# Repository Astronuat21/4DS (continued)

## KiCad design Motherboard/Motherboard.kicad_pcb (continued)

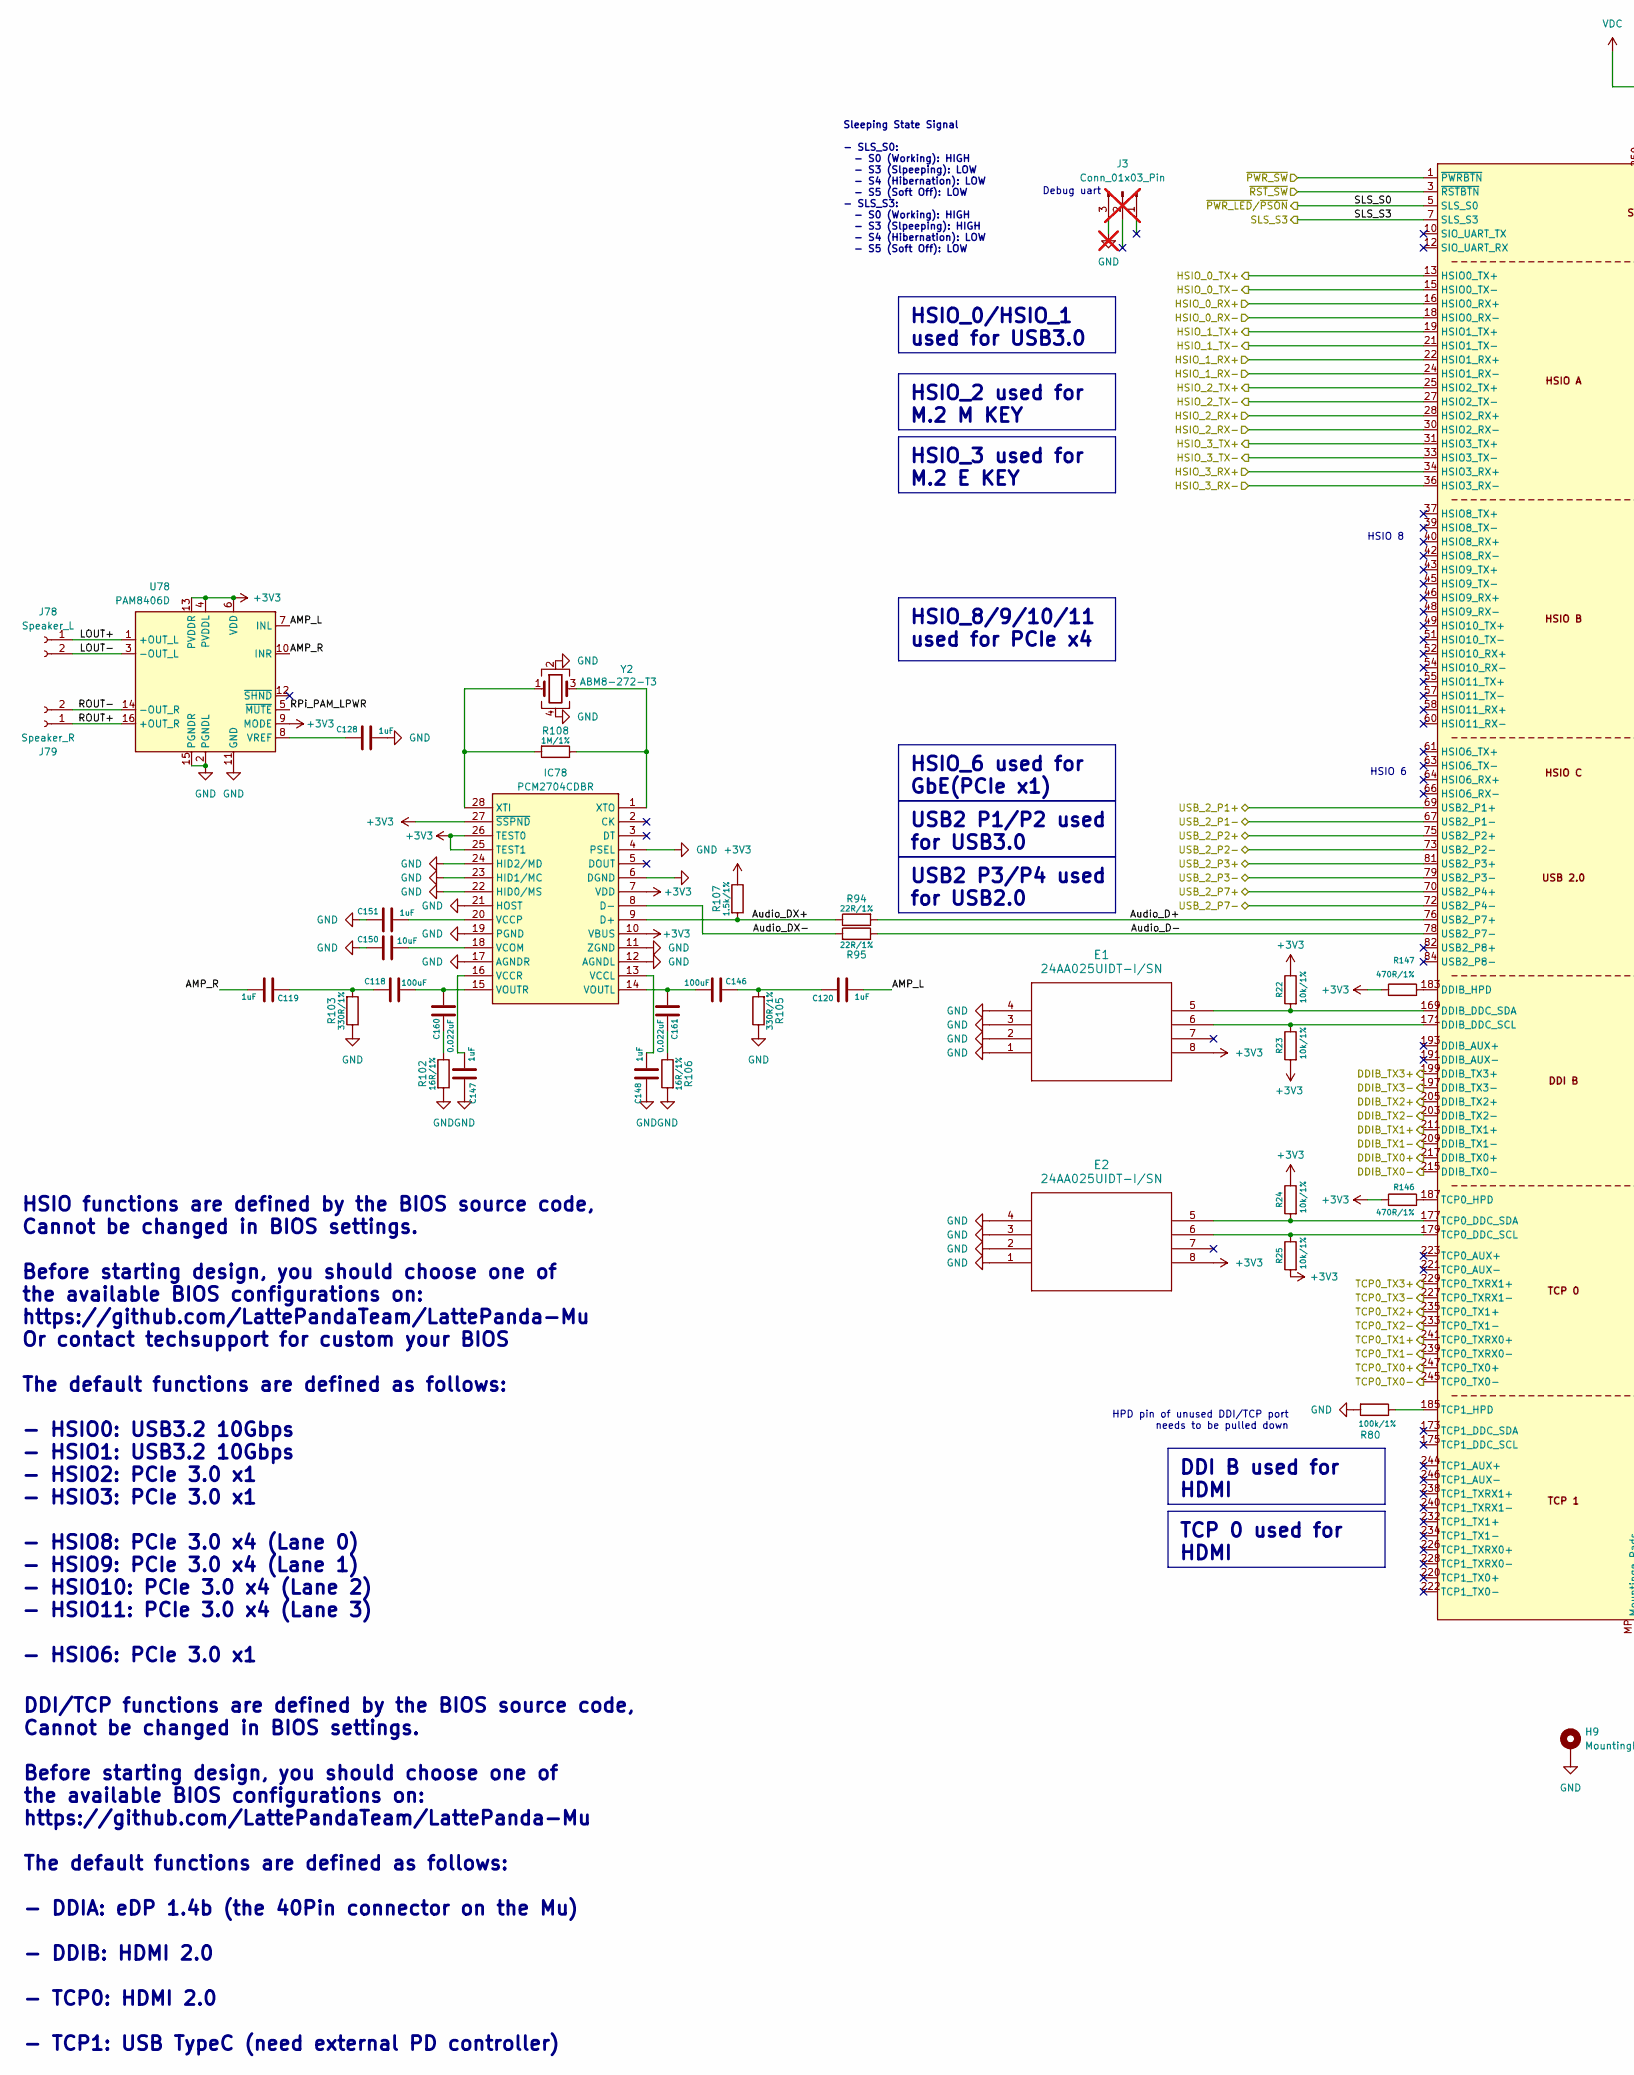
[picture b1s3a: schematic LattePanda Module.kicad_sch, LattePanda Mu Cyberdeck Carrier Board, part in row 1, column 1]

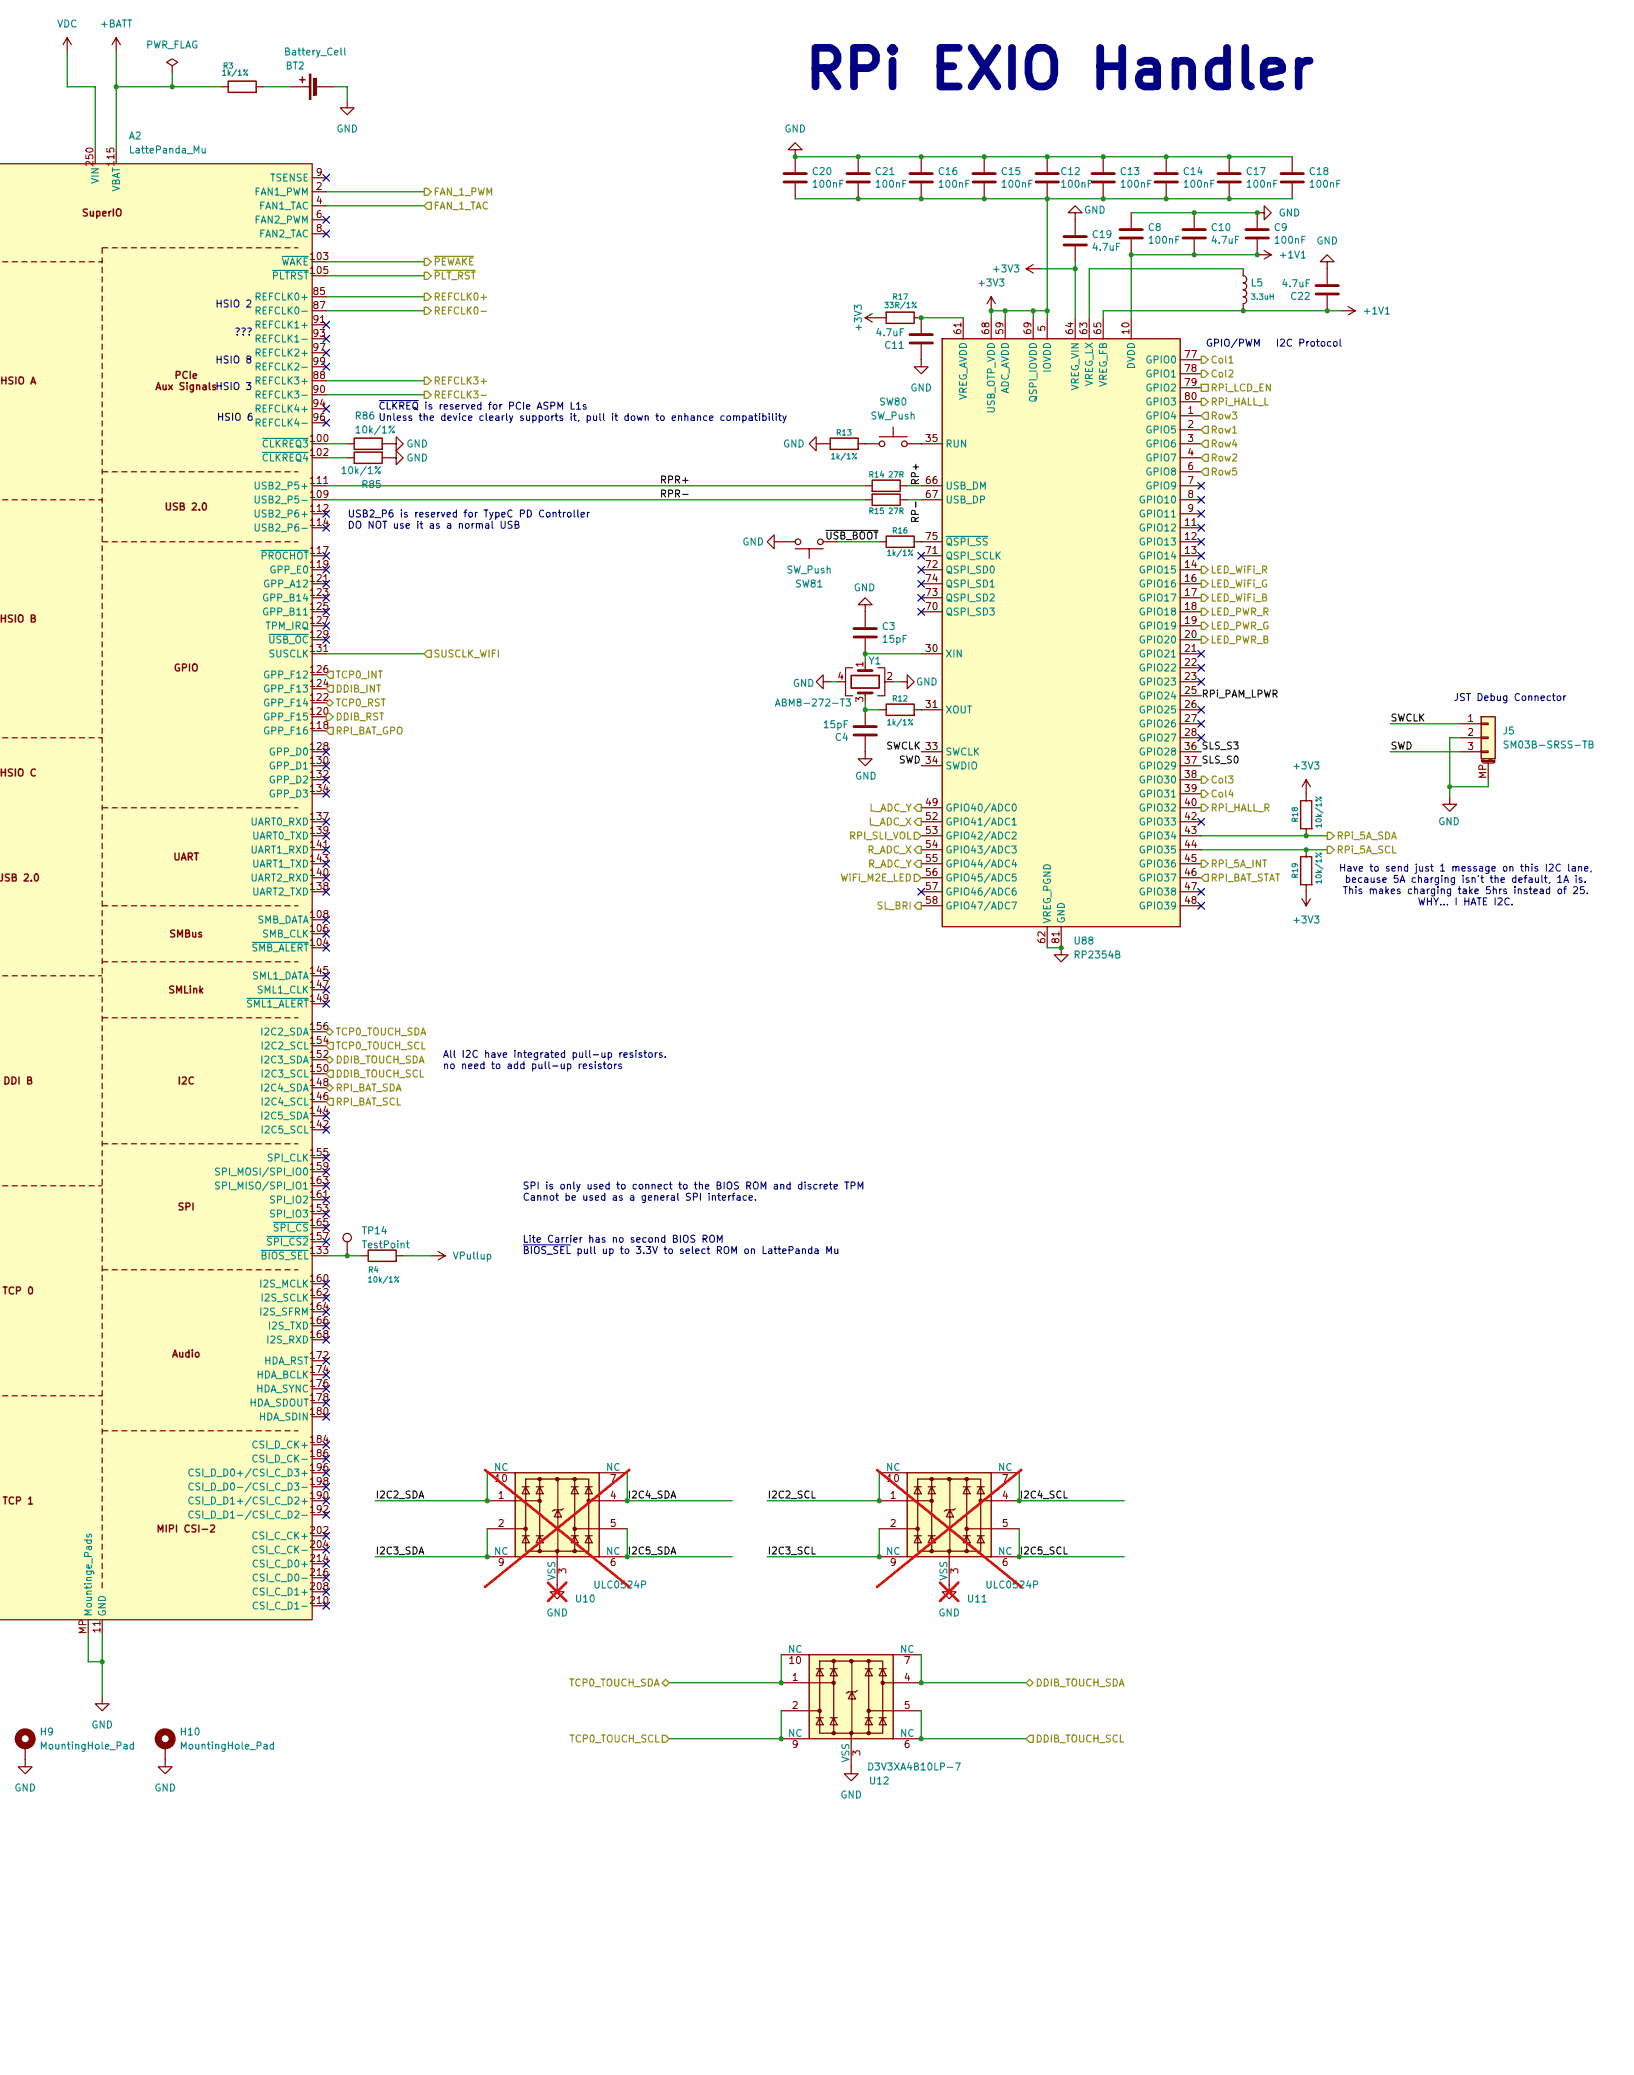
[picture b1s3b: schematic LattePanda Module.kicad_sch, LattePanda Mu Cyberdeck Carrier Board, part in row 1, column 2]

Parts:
A2: LattePanda_Mu; LattePanda_Module_H8.0mm_Horizontal; MPN ADDR0207-P001A
BT2: Battery_Cell; Battery_Holder_CR1220_S8411-45R; MPN BS-12-B3AA003
C3, C4: 15pF; C_0603_1608Metric; MPN C0603C150K4RACTU
C8, C9, C12, C13, C14, C15, C16, C17, C18, C20, C21: 100nF; C_0402_1005Metric; MPN CC0402MRX5R6BB104
C10, C11, C19, C22: 4.7uF; C_0402_1005Metric; MPN 0402X475M100NT
C118, C146: 100uF; C_1210_3225Metric; MPN GRM32ER61A107ME20L
C119, C120, C128, C147, C148, C151: 1uF; C_0402_1005Metric; MPN TCC0402X5R105M100AT
C150: 10uF; C_0402_1005Metric; MPN GMC04X5R106M10NT
C160, C161: 0.022uF; C_0603_1608Metric; MPN C0603X5R100-223KNP
E1, E2: 24AA025UIDT-I/SN; SOIC8-N_MC_MCH; MPN 24AA025UIDT-I/SN
H9, H10: MountingHole_Pad; MountingHole_3mm_M2_Pad_TopOnly; MPN SMTWEM225STR
IC78: PCM2704CDBR; SOP65P780X200-28N; MPN PCM2704CDBR
J3: Conn_01x03_Pin; PinHeader_1x03_P2.54mm_Vertical; not fitted
J5: SM03B-SRSS-TB; JST_SH_SM03B-SRSS-TB_1x03-1MP_P1.00mm_Horizontal; MPN SM03B-SRSS-TB
J78: Speaker_L; Molex_PicoBlade_53047-0210_1x02_P1.25mm_Vertical; MPN 0530470210
J79: Speaker_R; Molex_PicoBlade_53047-0210_1x02_P1.25mm_Vertical; MPN 0530470210
L5: 3.3uH; L_pol_2016; MPN AOTA-B201610S3R3-101-T
R3, R12, R13, R16: 1k/1%; R_0402_1005Metric; MPN CQ02WGF1001TCE
R4, R18, R19, R22, R23, R24, R25, R85, R86: 10k/1%; R_0402_1005Metric; MPN MCR01MZPF1002
R14, R15: 27R; R_0402_1005Metric; MPN AC0402FR-0727RL
R17: 33R/1%; R_0402_1005Metric; MPN AF0402FR-0733RL
R80: 100k/1%; R_0402_1005Metric; MPN SFR01MZPF1003
R94, R95: 22R/1%; R_0603_1608Metric; MPN 0603WAF220JT5E
R102, R106: 16R/1%; R_0805_2012Metric; MPN 0805W8F160JT5E
R103, R105: 330R/1%; R_0805_2012Metric; MPN TC0525F3300T5G
R107: 1.5k/1%; R_0805_2012Metric; MPN 0805W8F1501T5E
R108: 1M/1%; R_0603_1608Metric; MPN KTR03EZPF1004
R146, R147: 470R/1%; R_0402_1005Metric; MPN SFR01MZPF4700
SW80, SW81: SW_Push; SW_SPST_B3U-1000P; MPN B3U-1000P
TP14: TestPoint; TestPoint_Pad_D1.5mm
U10, U11: ULC0524P; Diodes_UDFN-10_1.0x2.5mm_P0.5mm; not fitted
U12: D3V3XA4B10LP-7; Diodes_UDFN-10_1x2.5mm_P0.5mm; MPN D3V3XA4B10LP-7
U78: PAM8406D; SOIC-16_3.9x9.9mm_P1.27mm
U88: RP2354B; QFN-80-1EP_10x10mm_P0.4mm_EP3.4x3.4mm; MPN SC1512-A4
Y1, Y2: ABM8-272-T3; Crystal_SMD_3225-4Pin_3.2x2.5mm; MPN ABM8-272-T3

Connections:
+1V1: C8.2, C9.2, C10.2, C22.1, L5.2, U88.10 (DVDD), U88.32 (DVDD), U88.51 (DVDD), U88.65 (VREG_FB)
+3V3: C12.2, C13.2, C14.2, C15.2, C16.2, C17.2, C18.2, C19.2, C20.2, C21.2, E1.8, E2.8, IC78.7 (VDD), IC78.10 (VBUS), IC78.25 (TEST1), IC78.26 (TEST0), IC78.27 (~SSPND), R17.2, R18.1, R19.2, R22.1, R23.2, R24.1, R25.2, R107.1, R146.1, R147.1, U78.4 (PVDDL), U78.6 (VDD), U78.9 (MODE), U78.13 (PVDDR), U88.5 (IOVDD), U88.15 (IOVDD), U88.24 (IOVDD), U88.29 (IOVDD), U88.41 (IOVDD), U88.50 (IOVDD), U88.59 (ADC_AVDD), U88.60 (IOVDD), U88.64 (VREG_VIN), U88.68 (USB_OTP_VDD), U88.69 (QSPI_IOVDD), U88.76 (IOVDD); also elsewhere on the board
+BATT: A2.115 (VBAT), R3.1
/EXIO/Col1: U88.77 (GPIO0); also elsewhere on the board
/EXIO/Col2: U88.78 (GPIO1); also elsewhere on the board
/EXIO/Col3: U88.38 (GPIO30); also elsewhere on the board
/EXIO/Col4: U88.39 (GPIO31); also elsewhere on the board
/EXIO/LED_PWR_B: U88.20 (GPIO20); also elsewhere on the board
/EXIO/LED_PWR_G: U88.19 (GPIO19); also elsewhere on the board
/EXIO/LED_PWR_R: U88.18 (GPIO18); also elsewhere on the board
/EXIO/LED_WiFi_B: U88.17 (GPIO17); also elsewhere on the board
/EXIO/LED_WiFi_G: U88.16 (GPIO16); also elsewhere on the board
/EXIO/LED_WiFi_R: U88.14 (GPIO15); also elsewhere on the board
/EXIO/L_ADC_X: U88.52 (GPIO41/ADC1); also elsewhere on the board
/EXIO/L_ADC_Y: U88.49 (GPIO40/ADC0); also elsewhere on the board
/EXIO/RPi_HALL_L: U88.80 (GPIO3); also elsewhere on the board
/EXIO/RPi_HALL_R: U88.40 (GPIO32); also elsewhere on the board
/EXIO/R_ADC_X: U88.54 (GPIO43/ADC3); also elsewhere on the board
/EXIO/R_ADC_Y: U88.55 (GPIO44/ADC4); also elsewhere on the board
/EXIO/Row1: U88.2 (GPIO5); also elsewhere on the board
/EXIO/Row2: U88.4 (GPIO7); also elsewhere on the board
/EXIO/Row3: U88.1 (GPIO4); also elsewhere on the board
/EXIO/Row4: U88.3 (GPIO6); also elsewhere on the board
/EXIO/Row5: U88.6 (GPIO8); also elsewhere on the board
/EXIO/SL_BRI: U88.58 (GPIO47/ADC7); also elsewhere on the board
/EXIO/SL_VOL: U88.53 (GPIO42/ADC2); also elsewhere on the board
/Fan_Temp/FAN_1_PWM: A2.2 (FAN1_PWM); also elsewhere on the board
/Fan_Temp/FAN_1_TAC: A2.4 (FAN1_TAC); also elsewhere on the board
/LattePanda Module/AMP_L: C120.1, U78.7 (INL)
/LattePanda Module/AMP_R: C119.1, U78.10 (INR)
/LattePanda Module/Audio_D+: A2.76 (USB2_P7+), R94.2
/LattePanda Module/Audio_D-: A2.78 (USB2_P7-), R95.1
/LattePanda Module/Audio_DX+: IC78.9 (D+), R94.1, R107.2
/LattePanda Module/Audio_DX-: IC78.8 (D-), R95.2
/LattePanda Module/DDIB_INT: A2.124 (GPP_F13); also elsewhere on the board
/LattePanda Module/DDIB_RST: A2.120 (GPP_F15); also elsewhere on the board
/LattePanda Module/DDIB_TOUCH_SCL: A2.150 (I2C3_SCL), U12.5, U12.6 (NC); also elsewhere on the board
/LattePanda Module/DDIB_TOUCH_SDA: A2.152 (I2C3_SDA), U12.4, U12.7 (NC); also elsewhere on the board
/LattePanda Module/DDIB_TX0+: A2.217 (DDIB_TX0+); also elsewhere on the board
/LattePanda Module/DDIB_TX0-: A2.215 (DDIB_TX0-); also elsewhere on the board
/LattePanda Module/DDIB_TX1+: A2.211 (DDIB_TX1+); also elsewhere on the board
/LattePanda Module/DDIB_TX1-: A2.209 (DDIB_TX1-); also elsewhere on the board
/LattePanda Module/DDIB_TX2+: A2.205 (DDIB_TX2+); also elsewhere on the board
/LattePanda Module/DDIB_TX2-: A2.203 (DDIB_TX2-); also elsewhere on the board
/LattePanda Module/DDIB_TX3+: A2.199 (DDIB_TX3+); also elsewhere on the board
/LattePanda Module/DDIB_TX3-: A2.197 (DDIB_TX3-); also elsewhere on the board
/LattePanda Module/HSIO_0_TX+: A2.13 (HSIO0_TX+); also elsewhere on the board
/LattePanda Module/HSIO_0_TX-: A2.15 (HSIO0_TX-); also elsewhere on the board
/LattePanda Module/HSIO_1_TX+: A2.19 (HSIO1_TX+); also elsewhere on the board
/LattePanda Module/HSIO_1_TX-: A2.21 (HSIO1_TX-); also elsewhere on the board
/LattePanda Module/HSIO_2_RX+: A2.28 (HSIO2_RX+); also elsewhere on the board
/LattePanda Module/HSIO_2_RX-: A2.30 (HSIO2_RX-); also elsewhere on the board
/LattePanda Module/HSIO_2_TX+: A2.25 (HSIO2_TX+); also elsewhere on the board
/LattePanda Module/HSIO_2_TX-: A2.27 (HSIO2_TX-); also elsewhere on the board
/LattePanda Module/HSIO_3_RX+: A2.34 (HSIO3_RX+); also elsewhere on the board
/LattePanda Module/HSIO_3_RX-: A2.36 (HSIO3_RX-); also elsewhere on the board
/LattePanda Module/HSIO_3_TX+: A2.31 (HSIO3_TX+); also elsewhere on the board
/LattePanda Module/HSIO_3_TX-: A2.33 (HSIO3_TX-); also elsewhere on the board
/LattePanda Module/LOUT+: J78.1, U78.1 (+OUT_L)
/LattePanda Module/LOUT-: J78.2, U78.3 (-OUT_L)
/LattePanda Module/REFCLK0+: A2.85 (REFCLK0+); also elsewhere on the board
/LattePanda Module/REFCLK0-: A2.87 (REFCLK0-); also elsewhere on the board
/LattePanda Module/REFCLK3+: A2.88 (REFCLK3+); also elsewhere on the board
/LattePanda Module/REFCLK3-: A2.90 (REFCLK3-); also elsewhere on the board
/LattePanda Module/ROUT+: J79.1, U78.16 (+OUT_R)
/LattePanda Module/ROUT-: J79.2, U78.14 (-OUT_R)
/LattePanda Module/RP+: R14.1, U88.66 (USB_DM)
/LattePanda Module/RP-: R15.1, U88.67 (USB_DP)
/LattePanda Module/RPI_BAT_GPO: A2.118 (GPP_F16); also elsewhere on the board
/LattePanda Module/RPI_BAT_SCL: A2.146 (I2C4_SCL); also elsewhere on the board
/LattePanda Module/RPI_BAT_SDA: A2.148 (I2C4_SDA); also elsewhere on the board
/LattePanda Module/RPI_BAT_STAT: U88.46 (GPIO37); also elsewhere on the board
/LattePanda Module/RPR+: A2.111 (USB2_P5+), R14.2
/LattePanda Module/RPR-: A2.109 (USB2_P5-), R15.2
/LattePanda Module/RPi_5A_INT: U88.45 (GPIO36); also elsewhere on the board
/LattePanda Module/RPi_5A_SCL: R19.1, U88.44 (GPIO35); also elsewhere on the board
/LattePanda Module/RPi_5A_SDA: R18.2, U88.43 (GPIO34); also elsewhere on the board
/LattePanda Module/RPi_LCD_EN: U88.79 (GPIO2); also elsewhere on the board
/LattePanda Module/RPi_PAM_LPWR: U78.5 (~MUTE), U88.25 (GPIO24)
/LattePanda Module/SLS_S3: A2.7 (SLS_S3), U88.36 (GPIO28); also elsewhere on the board
/LattePanda Module/SUSCLK_WIFI: A2.131 (SUSCLK); also elsewhere on the board
/LattePanda Module/SWCLK: J5.1, U88.33 (SWCLK)
/LattePanda Module/SWD: J5.3, U88.34 (SWDIO)
/LattePanda Module/TCP0_INT: A2.126 (GPP_F12); also elsewhere on the board
/LattePanda Module/TCP0_RST: A2.122 (GPP_F14); also elsewhere on the board
/LattePanda Module/TCP0_TOUCH_SCL: A2.154 (I2C2_SCL), U12.2, U12.9 (NC); also elsewhere on the board
/LattePanda Module/TCP0_TOUCH_SDA: A2.156 (I2C2_SDA), U12.1, U12.10 (NC); also elsewhere on the board
/LattePanda Module/TCP0_TX0+: A2.247 (TCP0_TX0+); also elsewhere on the board
/LattePanda Module/TCP0_TX0-: A2.245 (TCP0_TX0-); also elsewhere on the board
/LattePanda Module/TCP0_TX1+: A2.241 (TCP0_TXRX0+); also elsewhere on the board
/LattePanda Module/TCP0_TX1-: A2.239 (TCP0_TXRX0-); also elsewhere on the board
/LattePanda Module/TCP0_TX2+: A2.235 (TCP0_TX1+); also elsewhere on the board
/LattePanda Module/TCP0_TX2-: A2.233 (TCP0_TX1-); also elsewhere on the board
/LattePanda Module/TCP0_TX3+: A2.229 (TCP0_TXRX1+); also elsewhere on the board
/LattePanda Module/TCP0_TX3-: A2.227 (TCP0_TXRX1-); also elsewhere on the board
/LattePanda Module/USB_2_P7+: A2.70 (USB2_P4+); also elsewhere on the board
/LattePanda Module/USB_2_P7-: A2.72 (USB2_P4-); also elsewhere on the board
/LattePanda Module/WiFi_M2E_LED: U88.56 (GPIO45/ADC5); also elsewhere on the board
/LattePanda Module/~PWR_SW: A2.1 (~PWRBTN); also elsewhere on the board
/LattePanda Module/~RST_SW: A2.3 (~RSTBTN)
/LattePanda Module/~USB_BOOT: R16.1, SW81.1
/USB/CON_USB1_D_N: A2.79 (USB2_P3-)
/USB/CON_USB1_D_P: A2.81 (USB2_P3+)
/USB/CON_USB3_D_N: A2.73 (USB2_P2-); also elsewhere on the board
/USB/CON_USB3_D_P: A2.75 (USB2_P2+); also elsewhere on the board
/USB/CON_USB3_SSRX_N: A2.18 (HSIO0_RX-); also elsewhere on the board
/USB/CON_USB3_SSRX_P: A2.16 (HSIO0_RX+); also elsewhere on the board
/USB/CON_USB4_D_N: A2.67 (USB2_P1-); also elsewhere on the board
/USB/CON_USB4_D_P: A2.69 (USB2_P1+); also elsewhere on the board
/USB/CON_USB4_SSRX_N: A2.24 (HSIO1_RX-); also elsewhere on the board
/USB/CON_USB4_SSRX_P: A2.22 (HSIO1_RX+); also elsewhere on the board
/~PLT_RST: A2.105 (~PLTRST); also elsewhere on the board
/~PWR_LED/~PSON: A2.5 (SLS_S0), U88.37 (GPIO29); also elsewhere on the board
/~WAKE: A2.103 (~WAKE); also elsewhere on the board
GND: A2.11 (GND), A2.14 (GND), A2.17 (GND), A2.20 (GND), A2.23 (GND), A2.26 (GND), A2.29 (GND), A2.32 (GND), A2.35 (GND), A2.38 (GND), A2.41 (GND), A2.44 (GND), A2.47 (GND), A2.50 (GND), A2.53 (GND), A2.56 (GND), A2.59 (GND), A2.62 (GND), A2.65 (GND), A2.68 (GND), A2.71 (GND), A2.74 (GND), A2.77 (GND), A2.80 (GND), A2.83 (GND), A2.86 (GND), A2.89 (GND), A2.92 (GND), A2.95 (GND), A2.98 (GND), A2.101 (GND), A2.107 (GND), A2.110 (GND), A2.113 (GND), A2.116 (GND), A2.135 (GND), A2.136 (GND), A2.151 (GND), A2.158 (GND), A2.167 (GND), A2.170 (GND), A2.181 (GND), A2.182 (GND), A2.188 (GND), A2.189 (GND), A2.194 (GND), A2.195 (GND), A2.200 (GND), A2.201 (GND), A2.206 (GND), A2.207 (GND), A2.212 (GND), A2.213 (GND), A2.218 (GND), A2.219 (GND), A2.224 (GND), A2.225 (GND), A2.230 (GND), A2.231 (GND), A2.236 (GND), A2.237 (GND), A2.242 (GND), A2.243 (GND), A2.248 (GND), A2.249 (GND), A2.MP (Mountinge_Pads), BT2.2 (-), C3.1, C4.1, C8.1, C9.1, C10.1, C11.1, C12.1, C13.1, C14.1, C15.1, C16.1, C17.1, C18.1, C19.1, C20.1, C21.1, C22.2, C128.1, C147.2, C148.2, C150.2, C151.2, E1.1, E1.2, E1.3, E1.4, E2.1, E2.2, E2.3, E2.4, H9.1 (1_1), H10.1 (1_1), IC78.4 (PSEL), IC78.6 (DGND), IC78.11 (ZGND), IC78.12 (AGNDL), IC78.17 (AGNDR), IC78.19 (PGND), IC78.21 (HOST), IC78.22 (HID0/MS), IC78.23 (HID1/MC), IC78.24 (HID2/MD), J3.3, J5.2, J5.MP (MountPin), R13.1, R80.2, R85.2, R86.2, R102.2, R103.1, R105.1, R106.2, SW81.2, U10.3 (VSS), U10.8 (VSS), U11.3 (VSS), U11.8 (VSS), U12.3 (VSS), U12.8 (VSS), U78.2 (PGNDL), U78.11 (GND), U78.15 (PGNDR), U88.62 (VREG_PGND), U88.81 (GND), Y1.2, Y1.4, Y2.2, Y2.4; also elsewhere on the board
unnamed: A2.171 (DDIB_DDC_SCL), E1.6, R23.1
unnamed: A2.169 (DDIB_DDC_SDA), E1.5, R22.2
unnamed: A2.183 (DDIB_HPD), R147.2
unnamed: A2.179 (TCP0_DDC_SCL), E2.6, R25.1
unnamed: A2.177 (TCP0_DDC_SDA), E2.5, R24.2
unnamed: A2.187 (TCP0_HPD), R146.2
unnamed: A2.185 (TCP1_HPD), R80.1
unnamed: A2.133 (~BIOS_SEL), R4.1, TP14.1 (1_1)
unnamed: A2.100 (~CLKREQ3), R86.1
unnamed: A2.102 (~CLKREQ4), R85.1
unnamed: BT2.1 (+), R3.2
unnamed: C4.2, R12.1, Y1.3
unnamed: C118.2, C119.2, R103.2
unnamed: C120.2, C146.2, R105.2
unnamed: C160.2, R102.1
unnamed: C161.2, R106.1
unnamed: C148.1, IC78.13 (VCCL)
unnamed: C151.1, IC78.20 (VCCP)
unnamed: C147.1, IC78.16 (VCCR)
unnamed: C150.1, IC78.18 (VCOM)
unnamed: C146.1, C161.1, IC78.14 (VOUTL)
unnamed: C118.1, C160.1, IC78.15 (VOUTR)
unnamed: IC78.28 (XTI), R108.2, Y2.1
unnamed: IC78.1 (XTO), R108.1, Y2.3
unnamed: R13.2, SW80.1
unnamed: U10.1, U10.10 (NC)
unnamed: U10.2, U10.9 (NC)
unnamed: U10.4, U10.7 (NC)
unnamed: U10.5, U10.6 (NC)
unnamed: U11.1, U11.10 (NC)
unnamed: U11.2, U11.9 (NC)
unnamed: U11.4, U11.7 (NC)
unnamed: U11.5, U11.6 (NC)
unnamed: C128.2, U78.8 (VREF)
unnamed: SW80.2, U88.35 (RUN)
unnamed: C11.2, R17.1, U88.61 (VREG_AVDD)
unnamed: L5.1, U88.63 (VREG_LX)
unnamed: C3.2, U88.30 (XIN), Y1.1
unnamed: R12.2, U88.31 (XOUT)
unnamed: R16.2, U88.75 (~QSPI_SS)
VDC: A2.250 (VIN), A2.251 (VIN), A2.252 (VIN), A2.253 (VIN), A2.254 (VIN), A2.255 (VIN), A2.256 (VIN), A2.257 (VIN), A2.258 (VIN), A2.259 (VIN), A2.260 (VIN); also elsewhere on the board
VPullup: R4.2; also elsewhere on the board

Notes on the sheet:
HSIO functions are defined by the BIOS source code, Cannot be changed in BIOS settings. Before starting design, you should choose one of the available BIOS configurations on: https://github.com/LattePandaTeam/LattePanda-Mu Or contact techsupport for custom your BIOS The default functions are define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
HSIO 3
Lite Carrier has no second BIOS ROM ~{BIOS_SEL} pull up to 3.3V to select ROM on LattePanda Mu
DDI/TCP functions are defined by the BIOS source code, Cannot be changed in BIOS settings. Before starting design, you should choose one of the available BIOS configurations on: https://github.com/LattePandaTeam/LattePanda-Mu The default functions are defined as follows: - DDIA: eDP 1.4b (the 40Pin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
GPIO/PWM
HSIO 8
Sleeping State Signal - SLS_S0: - S0 (Working): HIGH - S3 (Slpeeping): LOW - S4 (Hibernation): LOW - S5 (Soft Off): LOW - SLS_S3: - S0 (Working): HIGH - S3 (Slpeeping): HIGH - S4 (Hibernation): LOW - S5 (Soft Off): LOW
HSIO 6
USB2_P6 is reserved for TypeC PD Controller DO NOT use it as a normal USB
SPI is only used to connect to the BIOS ROM and discrete TPM Cannot be used as a general SPI interface.
???
All I2C have integrated pull-up resistors. no need to add pull-up resistors
Debug uart
JST Debug Connector
~{CLKREQ} is reserved for PCIe ASPM L1s Unless the device clearly supports it, pull it down to enhance compatibility
RPi EXIO Handler
HSIO 8
Have to send just 1 message on this I2C lane, because 5A charging isn't the default, 1A is. This makes charging take 5hrs instead of 25. WHY... I HATE I2C.
I2C Protocol
HPD pin of unused DDI/TCP port needs to be pulled down
HSIO 2
HSIO_0/HSIO_1 used for USB3.0
HSIO_2 used for M.2 M KEY
HSIO_6 used for GbE(PCIe x1)
USB2 P3/P4 used for USB2.0
DDI B used for HDMI
TCP 0 used for HDMI
HSIO_3 used for M.2 E KEY
HSIO_8/9/10/11 used for PCIe x4
USB2 P1/P2 used for USB3.0

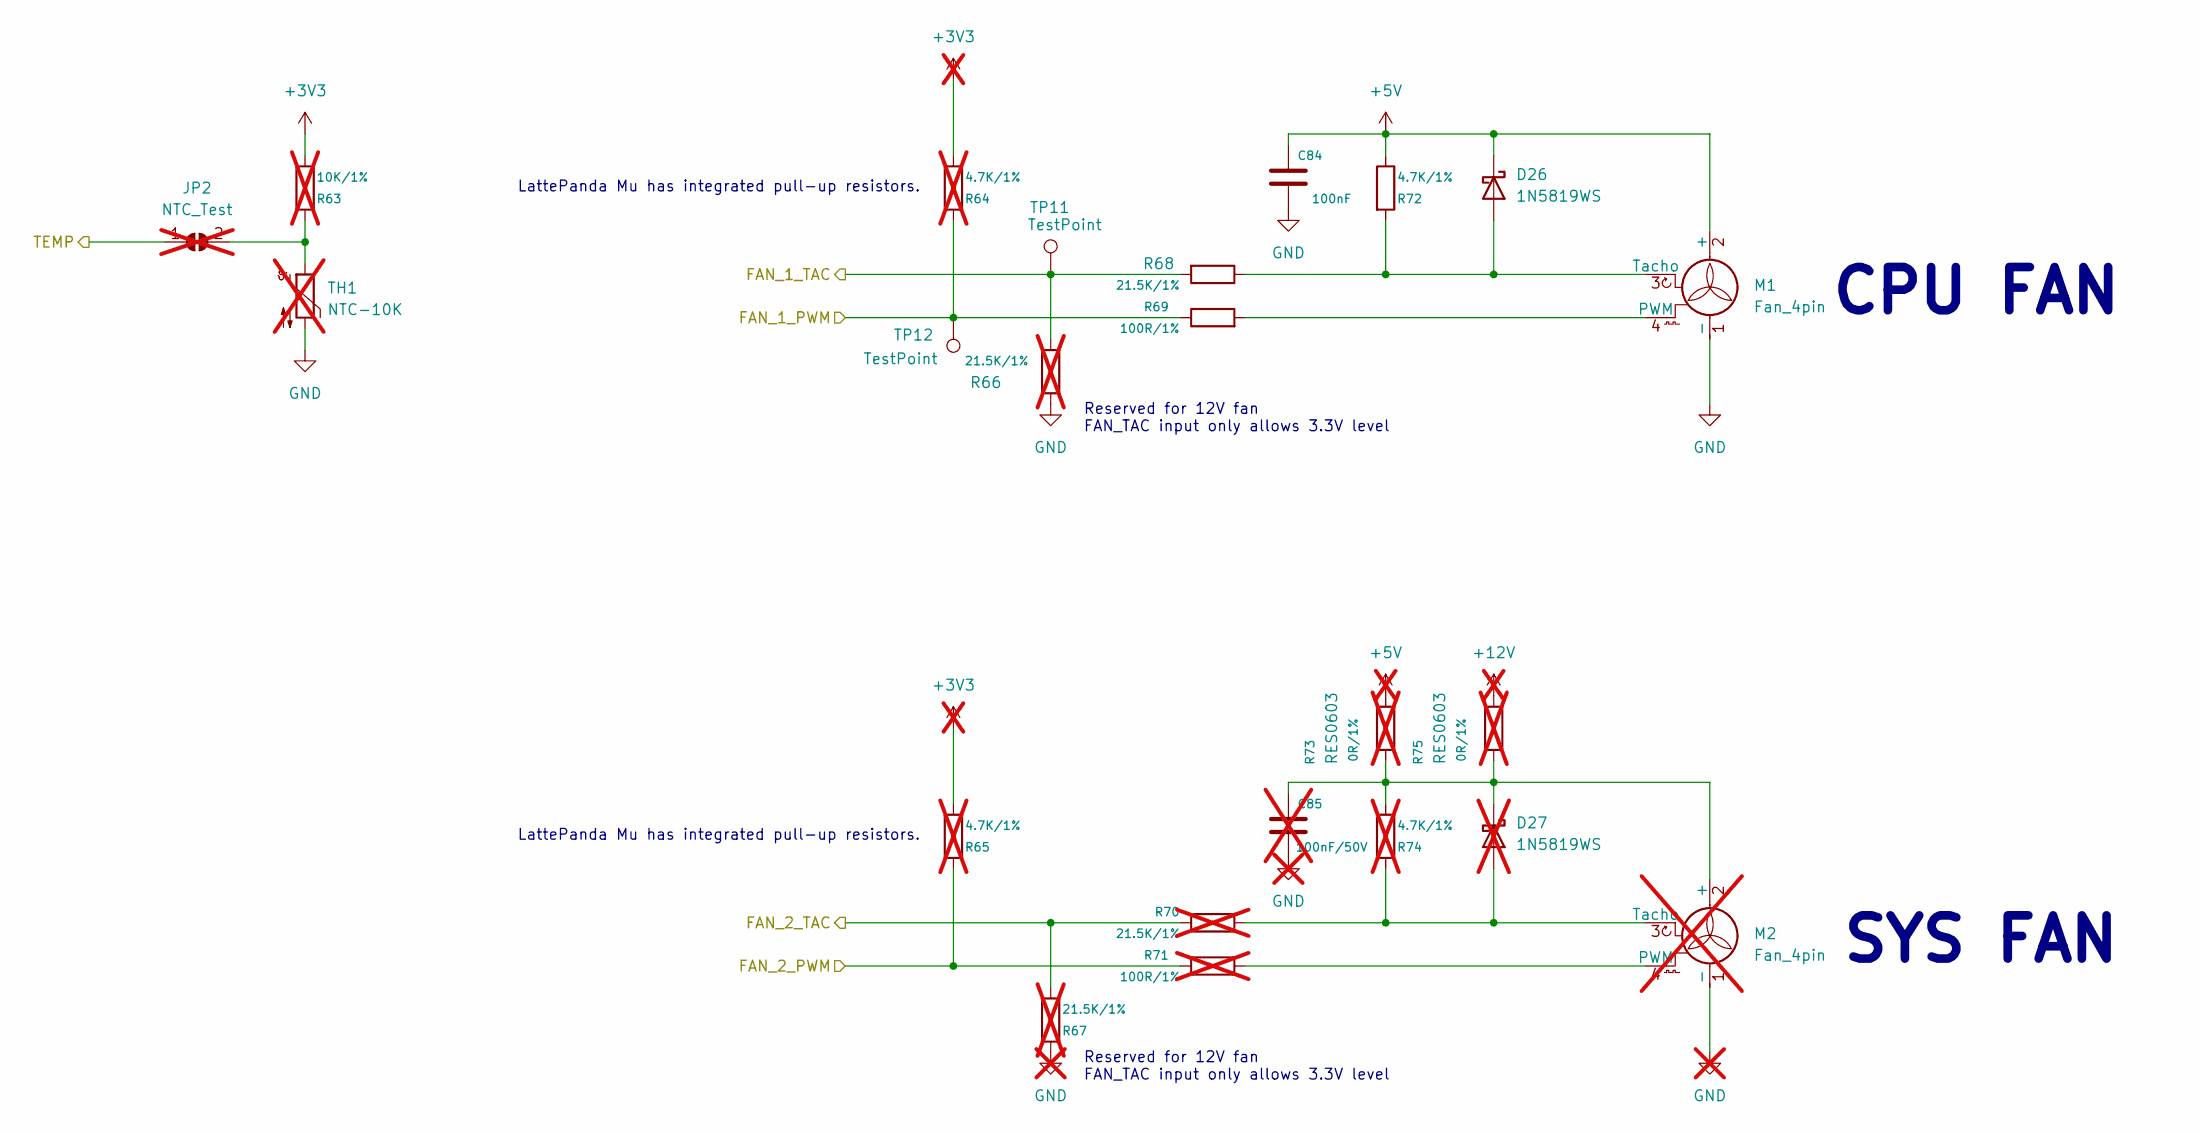
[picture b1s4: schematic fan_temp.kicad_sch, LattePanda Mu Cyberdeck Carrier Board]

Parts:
C84: 100nF; C_0402_1005Metric; MPN TCC0402X5R104M500AT
C85: 100nF/50V; C_0402_1005Metric; not fitted
D26: 1N5819WS; D_SOD-323; MPN 1N5819WS
D27: 1N5819WS; D_SOD-323; not fitted
JP2: NTC_Test; SolderJumper-2_P1.3mm_Open_RoundedPad1.0x1.5mm; not fitted
M1: Fan_4pin; JST_PH_B4B-PH-K_1x04_P2.00mm_Vertical
M2: Fan_4pin; JST_PH_B4B-PH-K_1x04_P2.00mm_Vertical; not fitted
R63: 10K/1%; R_0402_1005Metric; not fitted
R64, R65, R74: 4.7K/1%; R_0402_1005Metric; not fitted
R66, R67, R70: 21.5K/1%; R_0402_1005Metric; not fitted
R68: 21.5K/1%; R_0402_1005Metric; MPN 0402WGF2152TCE
R69: 100R/1%; R_0402_1005Metric; MPN AC0402FR-07100RL
R71: 100R/1%; R_0402_1005Metric; not fitted
R72: 4.7K/1%; R_0402_1005Metric; MPN CQ02WGF4701TCE
R73, R75: 0R/1%; RES0603; not fitted
TH1: NTC-10K; R_0603_1608Metric; not fitted
TP11, TP12: TestPoint; TestPoint_Pad_D1.5mm

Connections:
+5V: C84.1, D26.1 (K), M1.2 (+), R72.1, R73.2; also elsewhere on the board
/Fan_Temp/FAN_1_PWM: R64.2, R69.1, TP12.1 (1_1); also elsewhere on the board
/Fan_Temp/FAN_1_TAC: R66.1, R68.2, TP11.1 (1_1); also elsewhere on the board
GND: C84.2, C85.2, M1.1 (-), M2.1 (-), R66.2, R67.2, TH1.2; also elsewhere on the board
unnamed: C85.1, D27.1 (K), M2.2 (+), R73.1, R74.1, R75.1
unnamed 251: D26.2 (A), M1.3 (Tacho), R68.1, R72.2; also elsewhere on the board
unnamed: D27.2 (A), M2.3 (Tacho), R70.2, R74.2
unnamed: JP2.2 (B), R63.2, TH1.1
unnamed 297: M1.4 (PWM), R69.2; also elsewhere on the board
unnamed: M2.4 (PWM), R71.2
unnamed: R63.1, R64.1, R65.1
unnamed: R65.2, R71.1
unnamed: R67.1, R70.1

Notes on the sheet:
CPU FAN
SYS FAN
Reserved for 12V fan FAN_TAC input only allows 3.3V level
LattePanda Mu has integrated pull-up resistors.
